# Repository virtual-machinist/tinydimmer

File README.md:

# Tinydimmer

LED dimmer with 1-10V control using ATtiny85 microcontroller.

## Motivation

An existing 1-10V controlled LED dimmer in my bathroom doesn't work well with dimmable Osram Superstar 2700K 7.8W MR16 lamps. Its dimming range start is below the minimum power at which the LED lamps start reliably.  
As a result the lamps start with a sudden flash after 1/3 turn of the dimmer controller pot. The 1-10V controlled dimmer I have doesn't have any means to adjust the dimming range, so I had to build my own.

## Parts Used

Here are some notes about parts used for this project. As usual I tend to reuse parts left from previous projects and even something scavenged from broken electronics, so not all parts are listed here.  
The case was printed using black Prusament PETG leftovers from the MK3S printer upgrade (<100g consumed in total).  
The PCB was ordered from JLCPCB. They once again did a fantastic job with Gerbers to delivered PCB in under a week.

`RV1` - originally planned to use a plain MOV (7N431K), but after assembling decided to switch for a Bourns 14D271K GMOV (basically a MOV and a gas discharge tube in one package) for improved safety.

`TR1` - a Hahn EL 305 2051 9V 3W PCB transformer. Just had one laying around. Open circuit gives ~17V AC, drops to 9V AC under rated load.

`D1`..`D4` - 1N5819 Schottky diodes. According to spec can withstand up to 28V RMS reverse voltage with <0.6V drop. Used purely for low voltage drop to give `U1` LDO some margin.

`U1` - Rohm BAJ0CC0T 10V LDO regulator. Probably some other LDO regulator can do, but bear in mind that it must work with `9 x 1.41 - 2 x 0.6 - 10 = 1.49V` dropout if using a 9V AC transformer. Consider choosing another transformer and LM7810 to keep things simpler.

`U2` - Digispark USB clone with ATtiny85 onboard. Brains of the operation.

`J1`, `J2` - CamdenBoss CTB7000 series cut-to-length terminal blocks. Bought actually as CTB7000/36 and, well, cut to length.

`C1` - 820uF 25V low ESR Panasonic capacitor. Could have gotten away with a much smaller value (`U1` spec mandates at least 0.33uF), but just didn't want to put some off-brand ones with smaller value.

`C3` - 47uF 16V tantalum capacitor. According to `U1` spec should be fairly large (at least 22uF) to prevent output oscillation.

`C4`, `C5` - 0.1uF 25V ceramic capacitors. Probably not needed on an actual PCB, but somewhat improved stability while prototyping.

`Q1` - IRL540N, but can be any logic-level n-channel MOSFET having the same pinout.

`R1` - 560R 1/4W resistor to limit current for the 1-10V Busch-Jaeger electronic potentiometer. Spec says it can sink up to 50mA. When prototyping with 12V Vcc I used 1K.

`RV2` - a 25k pot looking like from [ACP](https://www.acptechnologies.com/). I advise to adjust it a notch _below_ dead center so that voltage on its wiper is 4.98-4.99V to be on the safe side. We can remap anything in software after all.

`HS1` and `HS2` were taken from an old ATX PSU. The one for `Q1` isn't actually needed as it barely gets warm with 490Hz PWM. The one for `U1` is recommended though.

## Operation Mode

When referring to microcontroller pins I use the pin layout from the Digispark USB clone I have (`P0`..`P5`).

After power on and boot:

1. `P0` is checked for `HIGH`.

2. If `HIGH`, the control voltage is read as an analog value is from `P2` and divided by 4.

3. If control voltage value is less than low threshold, the minimum PWM value is written to `P1` (in my case 16, i.e. 6% duty cycle).

4. If control voltage value is less than high threshold (in my case 240), the maximum PWM value (255) is written to `P1`. Done because control voltage is not actually 10V, but in 9.7..9.8V range.

5. If `P0` is `LOW`, 0 is written to `P1` turning LEDs completely off.

6. Sleep for 100ms.

## ~~Known Issues~~ Room for Improvement

* Currently the dimmer is powered on constantly since I haven't yet figured out how to program ATTiny85 without a bootloader (or with a minimal one). Default boot times are over 2 seconds. This consumes ~2W at all times, so can add up to ~20kWH a year. Will definitely be revisiting this. [#1](https://github.com/virtual-machinist/tinydimmer/issues/1)

* The case warped a bit after cooling and could use a couple of more screws in the middle of the lid. And/or latches. My FreeCAD-fu is weak ATM. [#2](https://github.com/virtual-machinist/tinydimmer/issues/2)

## Photos

Working prototype:

Starting PCB assembly:

Assembled PCB front:

Assembled PCB back:

Assembled case:

## Contributing

If you have any questions or remarks for this design, feel free to open an issue.

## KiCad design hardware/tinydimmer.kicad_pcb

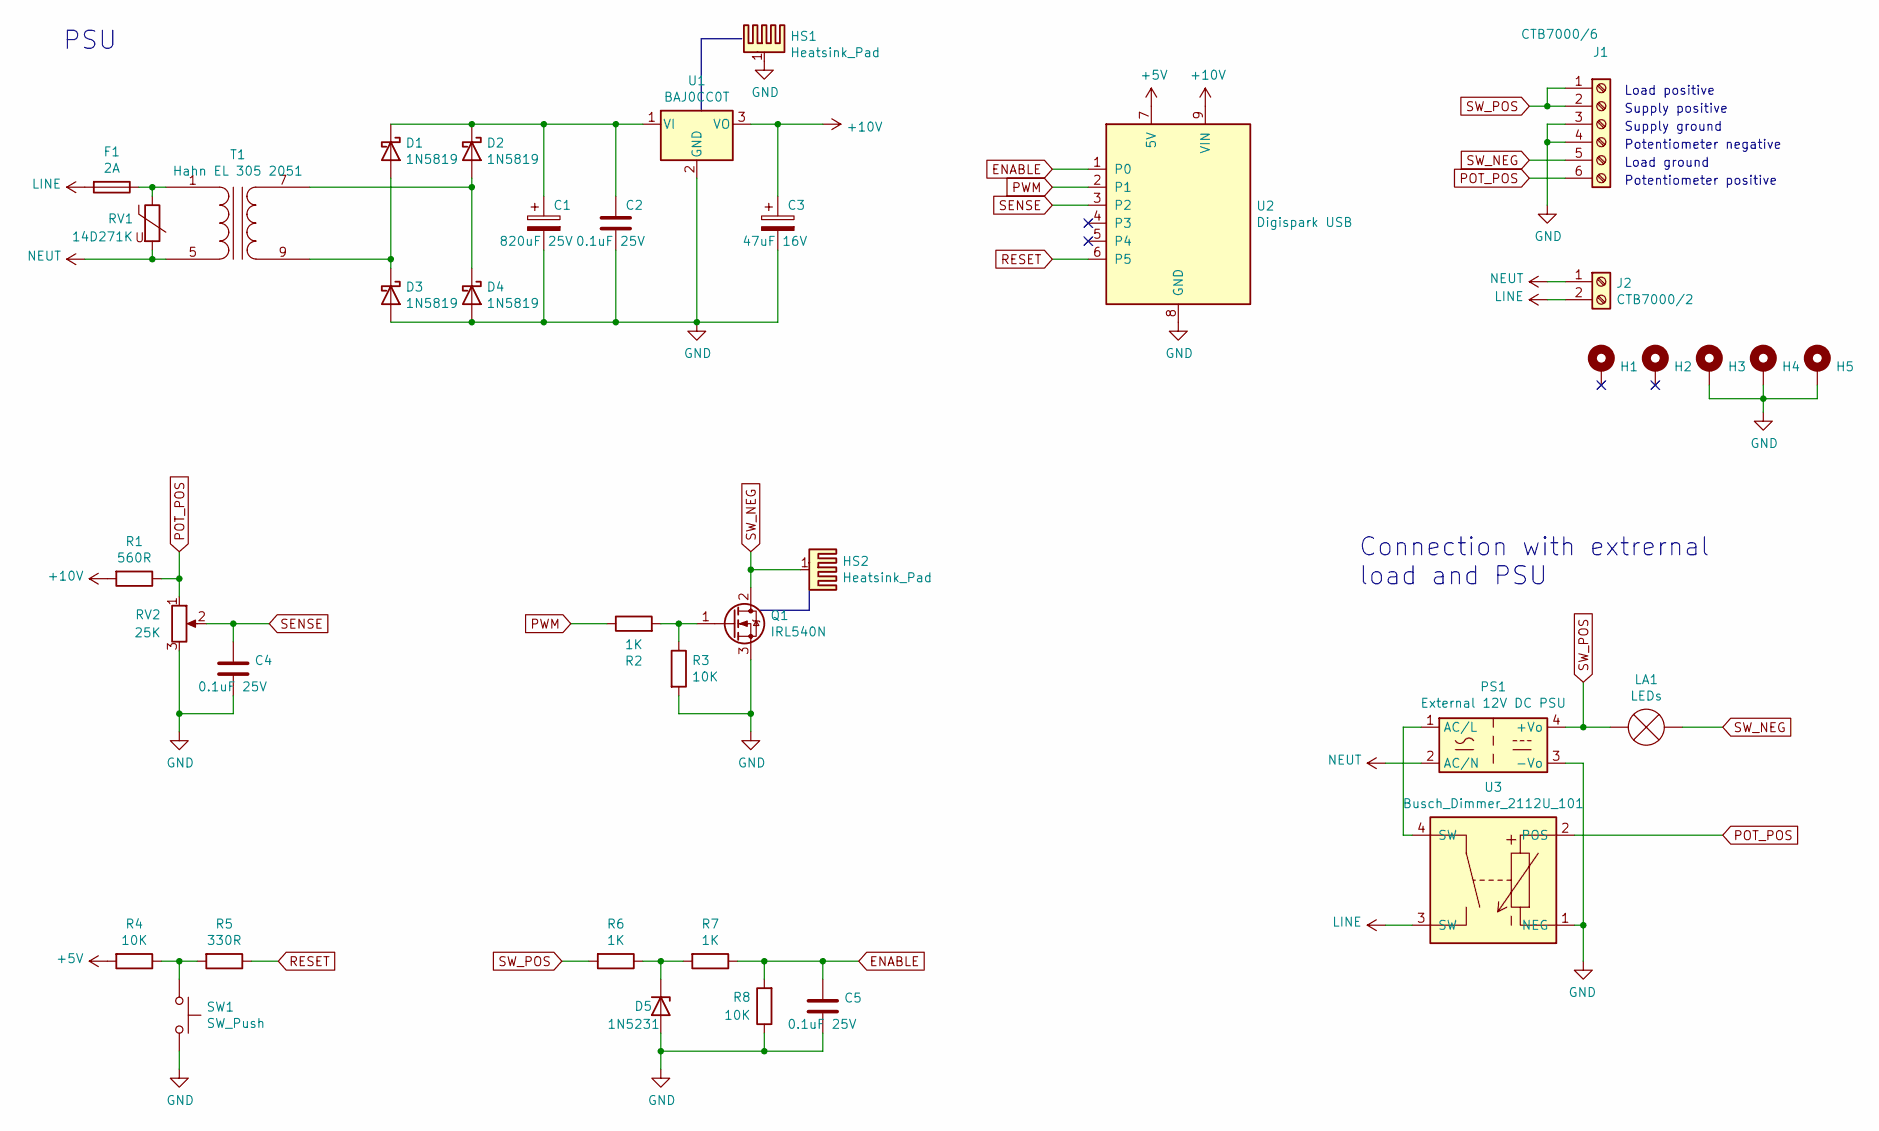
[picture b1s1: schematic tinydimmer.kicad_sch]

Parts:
C1: 820uF 25V; CP_Radial_D10.0mm_P5.00mm
C2, C4, C5: 0.1uF 25V; C_Disc_D6.0mm_W2.0mm_P3.81mm
C3: 47uF 16V; CP_Radial_Tantal_D5.5mm_P2.50mm
D1, D2, D3, D4: 1N5819; D_DO-41_SOD81_P10.16mm_Horizontal
D5: 1N5231; D_DO-35_SOD27_P7.62mm_Horizontal
F1: 2A; R_Axial_DIN0309_L9.0mm_D3.2mm_P12.70mm_Horizontal_Large_Pads
H1, H2, H3, H4, H5: MountingHole_Pad; MountingHole_3.2mm_M3_Pad
HS1, HS2: Heatsink_Pad; Heatsink_TO220_W23.5mm_L15.0mm_H30.0mm
J1: CTB7000/6; CamdenBoss_CTB7000_6_L30.0mm_P5.0mm
J2: CTB7000/2; CamdenBoss_CTB7000_2_L10.0mm_P5.0mm
LA1: LEDs
PS1: External 12V DC PSU
Q1: IRL540N; TO-220-3_Vertical
R1: 560R; R_Axial_DIN0207_L6.3mm_D2.5mm_P10.16mm_Horizontal
R2: 1K; R_Axial_DIN0207_L6.3mm_D2.5mm_P5.08mm_Vertical
R3: 10K; R_Axial_DIN0207_L6.3mm_D2.5mm_P5.08mm_Vertical
R4, R8: 10K; R_Axial_DIN0207_L6.3mm_D2.5mm_P10.16mm_Horizontal
R5: 330R; R_Axial_DIN0207_L6.3mm_D2.5mm_P10.16mm_Horizontal
R6, R7: 1K; R_Axial_DIN0207_L6.3mm_D2.5mm_P10.16mm_Horizontal
RV1: 14D271K; RV_Disc_D15.5mm_W3.9mm_P7.5mm
RV2: 25K; Potentiometer_ACP_CA6-V2,5_Vertical
SW1: SW_Push; SW_PUSH_6mm_H4.3mm
T1: Hahn EL 305 2051; Hahn_EL_305_2051
U1: BAJ0CC0T; TO-220-3_Vertical
U2: Digispark USB; Digispark_USB
U3: Busch_Dimmer_2112U_101

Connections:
+5V: R4.2, U2.7 (5V)
+10V: C3.1, R1.2, U1.3 (VO), U2.9 (VIN)
ENABLE: C5.1, R7.1, R8.2, U2.1 (P0)
GND: C1.2, C2.2, C3.2, C4.2, C5.2, D3.2 (A), D4.2 (A), D5.2 (A), H3.1, H4.1, H5.1, HS1.1, J1.3, J1.4, PS1.3 (-Vo), Q1.3 (S), R3.2, R8.1, RV2.3, SW1.2, U1.2 (GND), U2.8 (GND), U3.1 (NEG)
LINE: F1.2, J2.2, U3.3 (SW)
NEUT: J2.1, PS1.2 (AC/N), RV1.2, T1.5 (AB)
unnamed: C1.1, C2.1, D1.1 (K), D2.1 (K), U1.1 (VI)
unnamed: D1.2 (A), D3.1 (K), T1.9 (SA)
unnamed: D2.2 (A), D4.1 (K), T1.7 (SB)
unnamed: D5.1 (K), R6.1, R7.2
unnamed: F1.1, RV1.1, T1.1 (AA)
unnamed: PS1.1 (AC/L), U3.4 (SW)
unnamed: Q1.1 (G), R2.2, R3.1
unnamed: R4.1, R5.2, SW1.1
POT_POS: J1.6, R1.1, RV2.1, U3.2 (POS)
PWM: R2.1, U2.2 (P1)
RESET: R5.1, U2.6 (P5)
SENSE: C4.1, RV2.2, U2.3 (P2)
SW_NEG: HS2.1, J1.5, LA1.2 (+), Q1.2 (D)
SW_POS: J1.1, J1.2, LA1.1 (-), PS1.4 (+Vo), R6.2

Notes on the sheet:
Potentiometer negative
PSU
Supply ground
Supply positive
Potentiometer positive
Load positive
Load ground
Connection with extrernal load and PSU

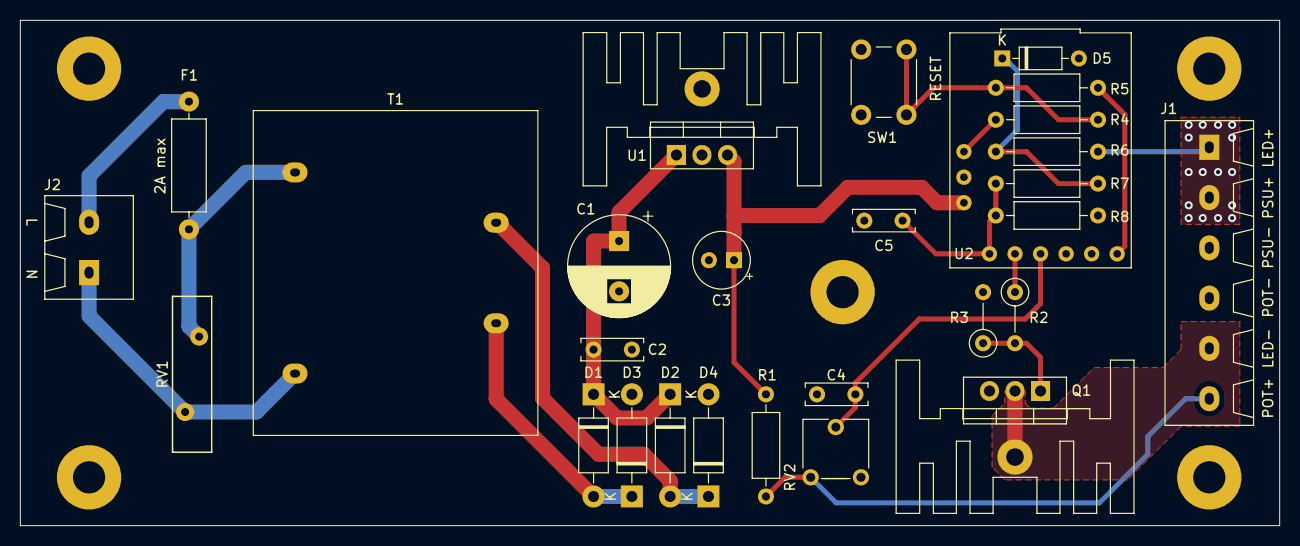
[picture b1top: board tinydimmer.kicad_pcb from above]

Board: 2 copper layers, 125.2 x 50.2 mm, 35 parts (0 on the bottom side), 19 nets.

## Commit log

2019-11-23 Initial commit
    Working Arduino prototype, custom symbols and footprints
    WIP: circuit diagram and PCB
2019-11-23 Adjust pads, rewire connectors, change footprints
2019-11-24 First PCB draft
2019-11-25 Make labels more visible
    Gerbers for first production batch
2019-12-13 Replace plain MOV with a protected GMOV
2019-12-13 Lower full power threshold, increase poll rate
2019-12-13 Simple housing in FreeCAD
2019-12-19 Project readme, photos
2019-12-19 Add license
2019-12-19 Link to issues
2023-02-03 Migrate to KiCad 6
